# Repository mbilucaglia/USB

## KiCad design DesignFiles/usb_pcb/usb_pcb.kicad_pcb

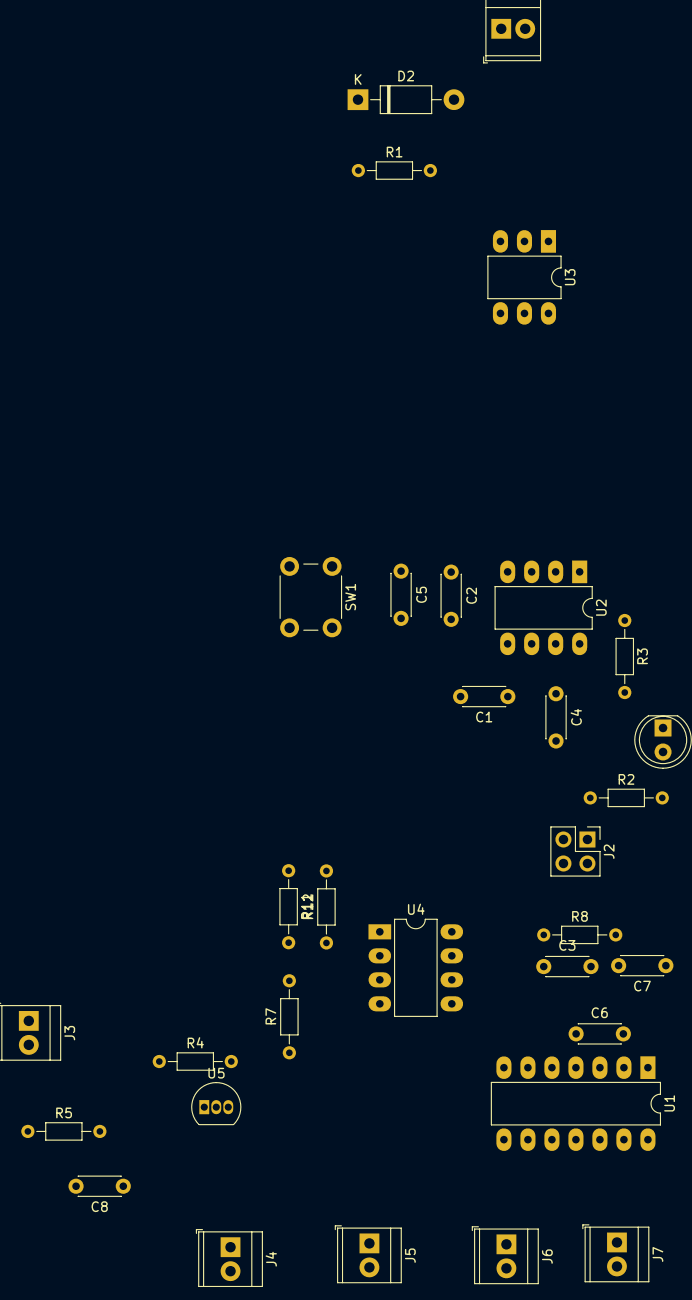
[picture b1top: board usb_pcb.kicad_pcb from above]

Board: 2 copper layers, 36 parts (0 on the bottom side), 20 nets, no tracks yet.

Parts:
C1: 10n; C_Disc_D4.3mm_W1.9mm_P5.00mm
C2, C6: 1u; C_Disc_D4.3mm_W1.9mm_P5.00mm
C3: 1n; C_Disc_D4.3mm_W1.9mm_P5.00mm
C4, C5, C7: 100n; C_Disc_D4.3mm_W1.9mm_P5.00mm
C8: 1u,35V; C_Disc_D4.3mm_W1.9mm_P5.00mm
D1: GREEN LED; LED_D5.0mm
D2: 1N4007; D_DO-41_SOD81_P10.16mm_Horizontal
H1, H2, H3, H4: MountingHole; MountingHole_3.2mm_M3
J1, J3, J4, J5, J6, J7: Screw_Terminal_01x02; TerminalBlock_TE_282834-2_1x02_P2.54mm_Horizontal
J2: Conn_01x04_Male; PinHeader_2x02_P2.54mm_Vertical
R1: 680R; R_Axial_DIN0204_L3.6mm_D1.6mm_P7.62mm_Horizontal
R2: 270R; R_Axial_DIN0204_L3.6mm_D1.6mm_P7.62mm_Horizontal
R3, R11, R12: 33k; R_Axial_DIN0204_L3.6mm_D1.6mm_P7.62mm_Horizontal
R4, R8: 100k; R_Axial_DIN0204_L3.6mm_D1.6mm_P7.62mm_Horizontal
R5: 100R; R_Axial_DIN0204_L3.6mm_D1.6mm_P7.62mm_Horizontal
R7: 18K; R_Axial_DIN0204_L3.6mm_D1.6mm_P7.62mm_Horizontal
SW1: SW_SPST; SW_PUSH_6mm_H5mm
U1: MCP6024-I/P; DIP-14_W7.62mm_LongPads
U2: NE555; DIP-8_W7.62mm_LongPads
U3: 4N35; DIP-6_W7.62mm_LongPads
U4: MCP6021-I/P; DIP-8_W7.62mm_LongPads
U5: L78L05_TO92; TO-92_Inline

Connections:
+5V: C2.1, C5.1, C6.1, C7.1, J2.2, R3.1, R11.1, SW1.1, U1.4, U2.4, U2.8, U3.5, U4.7, U5.1
/OUT_PULSE: J2.1, J2.3, R2.1, R8.2, U2.3
GND: C1.2, C2.2, C3.2, C4.2, C5.2, C6.2, C7.2, C8.2, D1.1, J2.4, J3.2, J4.2, J5.2, J6.2, J7.2, R5.1, R7.1, R12.2, U1.11, U2.1, U4.4, U5.2
unnamed: C1.1, U2.5
unnamed: C3.1, R8.1, U1.3, U1.5, U1.10, U1.12
unnamed: C4.1, R3.2, U2.6, U2.7
unnamed: C8.1, J7.1, U5.3
unnamed: D1.2, R2.2
unnamed: D2.1, R1.1
unnamed: D2.2, J1.1
unnamed: J1.2, U3.2
unnamed: J3.1, R4.1, R5.2
unnamed: J4.1, U1.6, U1.7
unnamed: J5.1, U1.8, U1.9
unnamed: J6.1, U1.13, U1.14
unnamed: R1.2, U3.1
unnamed: R4.2, U1.1, U1.2
unnamed: R7.2, SW1.2, U3.4
unnamed: R11.2, R12.1
unnamed: U2.2, U4.6

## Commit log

2020-03-25 added pcb design files
2020-03-25 added .gitignore to pcb project
2020-03-25 Schematic_modification
